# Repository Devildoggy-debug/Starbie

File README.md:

## <ins>Starbie</ins>
## <ins>What it is</ins>
It is a tiny motion-controlled digital pet: basically a desktop Tamagotchi with minimal gameplay buttons. Instead of pressing controls, you interact with it by physically moving the board.
Basically supposed to act like a digital pet with a physical body
<br>
## <ins>Reason for making it</ins>
I made it as part of half life. I chose to make Starbie since I didn't have much experience in making a PCB,so I decided to take the starter guide and made a starbie
The Starbie generally works due to a XIAO ESP32 C3 chip as the main microcontroller. It has environment sensors to detect motion,Two buttons, and a display which is used to show the pet.
## <ins>Uniqueness</ins>
My Starbie is distinct in that it has LEDs powered by a 3V battery and controlled by two Push buttons which work based on the pressure applied on them 
Its also incredibly well drawn (sarcasm)
<br>
Below are the schematic,3D model and PCB display of My Starbie 

<br>

<br>

BOM for Dusk:

### Bill of Materials (BOM)

| Reference | Qty | Value | Cost | Website | Footprint | Datasheet |
| :--- | :---: | :--- | :---: | :---: | :--- | :---: |
| BT1 (Battery holder) | 1 | | $0.50 | [Link](https://in.element14.com/keystone/3034tr/battery-contact-coin-cell-20mm/dp/2959382) | Battery:BatteryHolder_Keystone_3034_1x20mm | |
| D1,D2 | 1 | LED | $0.05 | [Link](https://techtonics.in/product/5mm-round-white-led-2pin/?srsltid=AU7gw4WYyVBFoiB5SX1NkU9sesHsxuXcRevhFP9Q3OYVX5no6MHSYKCl9d4) | LED_THT:LED_D5.0mm | |
| J1 | 1 | Conn_01x04_MountingPin | $2.07 | [Link](https://techtonics.in/product/0-96-inch-i2c-iic-128x64-oled-display-module-4-pin-yellow-blue-color/?srsltid=AU7gw4URHwcidTIcFkySu7G90KVIEDv9nnOj5pwqBi-oZm4BpHAqL1xlpSU) | Imported Parts:Display_128x64_096_I2C | |
| J2 | 1 | Conn_01x08_MountingPin | $3.61 | [Link](https://www.amazon.in/SHOKITECH-2-54mm-Single-Straight-Header/dp/B0CM7H4SPM) | Connector_PinHeader_2.54mm:PinHeader_1x08_P2.54mm_Vertical | |
| R1 | 1 | 10K | $0.70 | [Link](https://in.element14.com/vishay/mba02040c1002fc100/res-10k-1-400mw-axial-thin-film/dp/2614354) | Resistor_THT:R_Axial_DIN0204_L3.6mm_D1.6mm_P7.62mm_Horizontal | |
| R2,R3 | 1 | 220 | $1.62 | [Link](https://in.element14.com/vishay/mbb02070c2200fct00/res-220r-0-6w-axial-metal-film/dp/3546954) | Resistor_THT:R_Axial_DIN0207_L6.3mm_D2.5mm_P7.62mm_Horizontal | |
| SW1,SW2 | 1 | SW_Push | $4.49 | [Link](https://neomacro.in/products/cherry-mx-switches?srsltid=AU7gw4XISCDAMECzFsRSF6n9Iz9YlAOe0Jn77wQGhb9YwPDikEzn6JcmHIo) | Button_Switch_Keyboard:SW_Cherry_MX_1.00u_PCB | |
| SW3,SW4 | 1 | SW_Push | $0.10 | [Link](https://techtonics.in/product/tactile-push-button-switch-4-pin-6x6x5-pack-of-10/) | Button_Switch_THT:SW_PUSH_6mm | |
| U1 | 1 | XIAO-ESP32-C3-SMD | $7.23 | [Link](https://thinkrobotics.com/products/seeed-studio-xiao-rp2040?variant=47933480173885&country=IN&currency=INR&utm_medium=product_sync&utm_source=google&utm_content=sag_organic&utm_campaign=sag_organic&utm_source=googleads&utm_medium=cpc&utm_source=SR_google&utm_medium=pmax&utm_campaign=PMax_Shopping_IN_SR467-17456069194&utm_content=-&gad_source=1&gad_campaignid=18239908785&gclid=CjwKCAjw56zWBhB0EiwAdPOQOf6IgNz5R3BqPwlQqQl8AWVahfhugwIoGKNaa2ns9PY7rDB2DrE_2hoC0ywQAvD_BwE) | Imported Parts:XIAO-ESP32-C6-DIP | |
| U2 | 1 | DHT11 | $2.68 | [Link](https://www.amazon.in/DHT11-temperature-and-humidity-sensor/dp/B0D78NP6GQ/ref=pd_lpo_d_sccl_2/524-7894693-3720055?pd_rd_w=lEKtF&content-id=amzn1.sym.e0c8139c-1aa1-443c-af8a-145a0481f27c&pf_rd_p=e0c8139c-1aa1-443c-af8a-145a0481f27c&pf_rd_r=4SEVF1R5ZT1XHH57YXY0&pd_rd_wg=0lrlF&pd_rd_r=bfad8e95-3a74-4bf9-a463-96e847242546&pd_rd_i=B0D78NP6GQ&psc=1) | Sensor:Aosong_DHT11_5.5x12.0_P2.54mm | [Datasheet](http://akizukidenshi.com/download/ds/aosong/DHT11.pdf) |
| Battery | 1 | 3V | $2.07 | [Link](https://www.amazon.in/CR2032-Lithium-Coin-Battery-pcs/dp/B0CXKL8DC1?source=ps-sl-shoppingads-lpcontext&ref_=fplfs&psc=1&smid=AJ6SIZC8YQDZX) | | |

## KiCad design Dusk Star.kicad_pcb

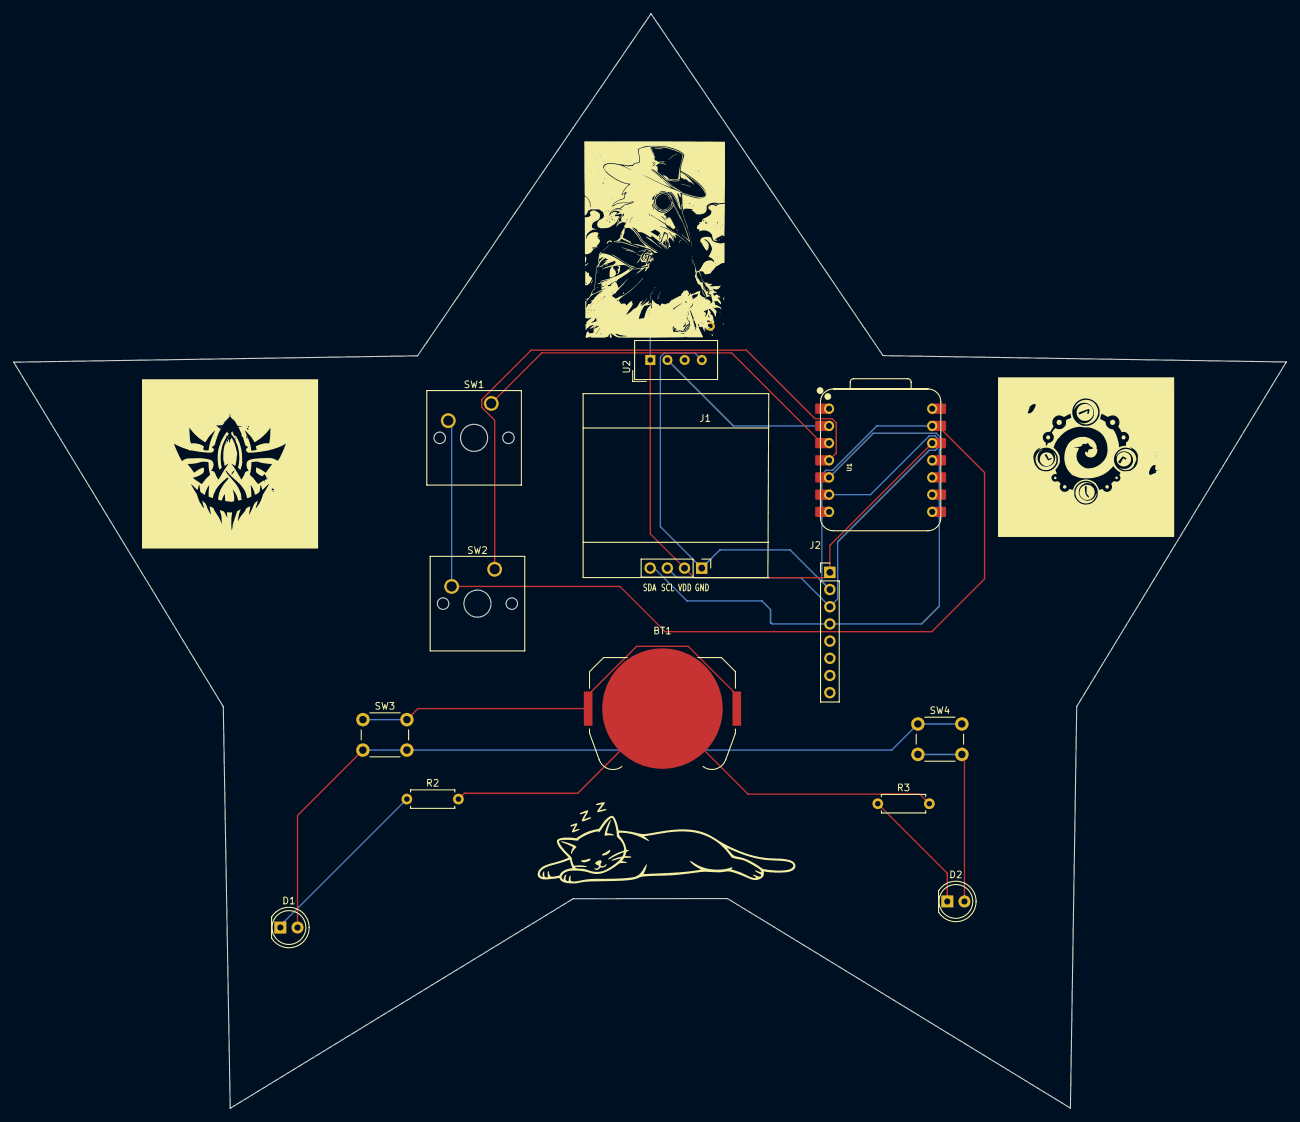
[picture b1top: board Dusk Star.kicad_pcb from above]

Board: 2 copper layers, 188.1 x 161.8 mm, 14 parts (0 on the bottom side), 13 nets.

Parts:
BT1: 3V; BatteryHolder_Keystone_3034_1x20mm
D1, D2: LED; LED_D5.0mm
J1: Conn_01x04_MountingPin; Display_128x64_096_I2C
J2: Conn_01x08_MountingPin; PinHeader_1x08_P2.54mm_Vertical
R1: 10K; R_Axial_DIN0204_L3.6mm_D1.6mm_P7.62mm_Horizontal
R2, R3: 220; R_Axial_DIN0207_L6.3mm_D2.5mm_P7.62mm_Horizontal
SW1, SW2: SW_Push; SW_Cherry_MX_1.00u_PCB
SW3, SW4: SW_Push; SW_PUSH_6mm
U1: XIAO-ESP32-C3-SMD; XIAO-ESP32-C6-DIP
U2: DHT11; Aosong_DHT11_5.5x12.0_P2.54mm

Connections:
+3.3V: J1.2, J2.1, R1.1, U1.12 (3V3_OUT), U2.1 (VDD)
/DHT11 DATA: U1.2 (D1), U2.2 (DATA)
/GPIO 2: SW1.1, U1.3 (D2)
/GPIO 3: SW2.1, U1.4 (D3)
/SCL: J1.4, J2.4, U1.5 (D4)
/SDA: J1.3, J2.3, U1.6 (D5)
GND: J1.1, J2.2, SW1.2, SW2.2, U1.13 (GND), U2.4 (GND)
unnamed: BT1.1 (+), SW3.1
unnamed: BT1.2 (-), R2.2, R3.2
unnamed: D1.2 (A), SW3.2, SW4.1
unnamed: D1.1 (K), R2.1
unnamed: D2.2 (A), SW4.2
unnamed: D2.1 (K), R3.1

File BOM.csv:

Item,Qty,Supplier,Cost/item,Total Cost,link
Battery Holder,1,Element 14,$0.50,$0.50,https://in.element14.com/keystone/3034tr/battery-contact-coi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
LED,1,Techtonics,$0.05,$0.05,https://techtonics.in/product/5mm-round-white-led-2pin/?srsl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
Conn_01x04_MountingPin,1,Techtonics,$2.07,$2.07,https://techtonics.in/product/0-96-inch-i2c-iic-128x64-oled-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
Conn_01x08_MountingPin,1,Amazon,$3.61,$3.61,https://www.amazon.in/SHOKITECH-2-54mm-Single-Straight-Heade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
10K,1,Element 14,$0.70,$0.70,https://in.element14.com/vishay/mba02040c1002fc100/res-10k-1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
220,1,Element 14,$1.62,$1.62,https://in.element14.com/vishay/mbb02070c2200fct00/res-220r-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
SW_Push,1,Neo Macro,$4.49,$4.49,https://neomacro.in/products/cherry-mx-switches?srsltid=AU7g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
SW_Push,1,Techtonics,$0.10,$0.10,https://techtonics.in/product/tactile-push-button-switch-4-p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
XIAO-ESP32-C3-SMD,1,Think Robotics,$7.23,$7.23,https://thinkrobotics.com/products/seeed-studio-xiao-rp2040?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
DHT11,1,Amazon,$2.68,$2.68,https://www.amazon.in/DHT11-temperature-and-humidity-sensor/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
3V Battery,1,Amazon,$2.07,$2.07,https://www.amazon.in/CR2032-Lithium-Coin-Battery-pcs/dp/B0C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
Estimated total shipping,1,,,$3.00,
